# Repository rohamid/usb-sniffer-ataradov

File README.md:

# USB Sniffer #
This repository is for modified hardware of [ataradov's USB-sniffer](https://github.com/ataradov/usb-sniffer). I re-design this hardware because I don't want to use the 3d print case. I like to use the aluminum case.

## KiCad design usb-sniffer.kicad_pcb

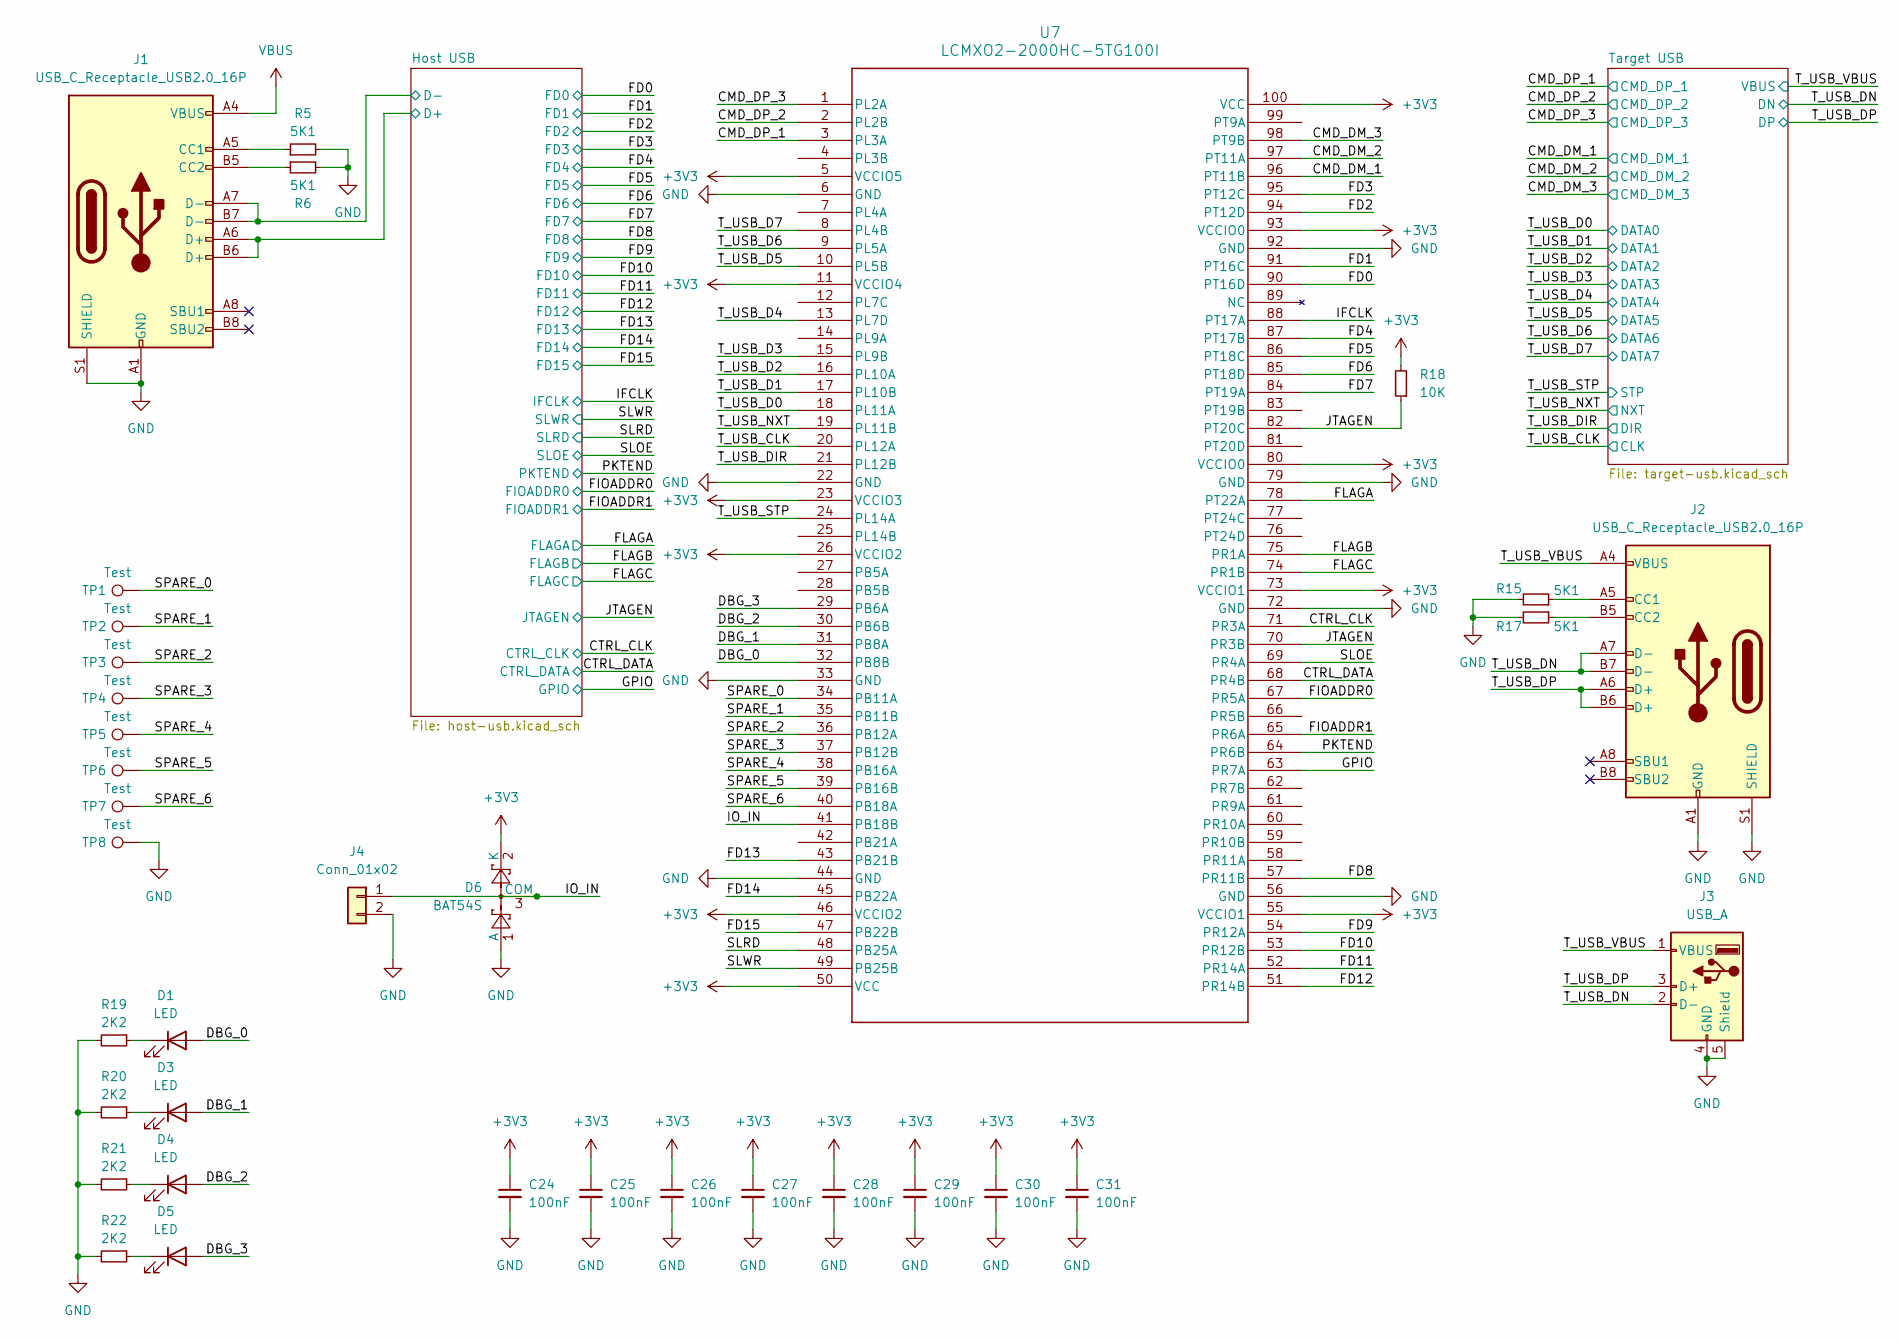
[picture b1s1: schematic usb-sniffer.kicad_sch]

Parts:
C24, C25, C26, C27, C28, C29, C30, C31: 100nF; C_0402_1005Metric
D1, D3, D4, D5: LED; LED_0603_1608Metric
D6: BAT54S; SOT-23
J1, J2: USB_C_Receptacle_USB2.0_16P; USB_C_Receptacle_G-Switch_GT-USB-7010ASV
J3: USB_A; USB_A_Molex_67643_Horizontal
J4: Conn_01x02; PinHeader_1x02_P2.54mm_Vertical
R5, R6, R15, R17: 5K1; R_0402_1005Metric
R18: 10K; R_0402_1005Metric
R19, R20, R21, R22: 2K2; R_0402_1005Metric
TP1, TP2, TP3, TP4, TP5, TP6, TP7, TP8: Test; TestPoint_Pad_D1.0mm
U7: LCMXO2-2000HC-5TG100I; LQFP-100_14x14mm_P0.5mm

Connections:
+3V3: C24.1, C25.1, C26.1, C27.1, C28.1, C29.1, C30.1, C31.1, D6.2 (K), R18.2, U7.5 (VCCIO5), U7.11 (VCCIO4), U7.23 (VCCIO3), U7.26 (VCCIO2), U7.46 (VCCIO2), U7.50 (VCC), U7.55 (VCCIO1), U7.73 (VCCIO1), U7.80 (VCCIO0), U7.93 (VCCIO0), U7.100 (VCC); also elsewhere on the board
/CMD_DM_1: U7.96 (PT11B); also elsewhere on the board
/CMD_DM_2: U7.97 (PT11A); also elsewhere on the board
/CMD_DM_3: U7.98 (PT9B); also elsewhere on the board
/CMD_DP_1: U7.3 (PL3A); also elsewhere on the board
/CMD_DP_2: U7.2 (PL2B); also elsewhere on the board
/CMD_DP_3: U7.1 (PL2A); also elsewhere on the board
/CTRL_CLK: U7.71 (PR3A); also elsewhere on the board
/CTRL_DATA: U7.68 (PR4B); also elsewhere on the board
/DBG_0: D1.2 (A), U7.32 (PB8B)
/DBG_1: D3.2 (A), U7.31 (PB8A)
/DBG_2: D4.2 (A), U7.30 (PB6B)
/DBG_3: D5.2 (A), U7.29 (PB6A)
/FD0: U7.90 (PT16D); also elsewhere on the board
/FD1: U7.91 (PT16C); also elsewhere on the board
/FD2: U7.94 (PT12D); also elsewhere on the board
/FD3: U7.95 (PT12C); also elsewhere on the board
/FD4: U7.87 (PT17B); also elsewhere on the board
/FD5: U7.86 (PT18C); also elsewhere on the board
/FD6: U7.85 (PT18D); also elsewhere on the board
/FD7: U7.84 (PT19A); also elsewhere on the board
/FD8: U7.57 (PR11B); also elsewhere on the board
/FD9: U7.54 (PR12A); also elsewhere on the board
/FD10: U7.53 (PR12B); also elsewhere on the board
/FD11: U7.52 (PR14A); also elsewhere on the board
/FD12: U7.51 (PR14B); also elsewhere on the board
/FD13: U7.43 (PB21B); also elsewhere on the board
/FD14: U7.45 (PB22A); also elsewhere on the board
/FD15: U7.47 (PB22B); also elsewhere on the board
/FIOADDR0: U7.67 (PR5A); also elsewhere on the board
/FIOADDR1: U7.65 (PR6A); also elsewhere on the board
/FLAGA: U7.78 (PT22A); also elsewhere on the board
/FLAGB: U7.75 (PR1A); also elsewhere on the board
/FLAGC: U7.74 (PR1B); also elsewhere on the board
/GPIO: U7.63 (PR7A); also elsewhere on the board
/Host USB/D+: J1.A6 (D+), J1.B6 (D+); also elsewhere on the board
/Host USB/D-: J1.A7 (D-), J1.B7 (D-); also elsewhere on the board
/IFCLK: U7.88 (PT17A); also elsewhere on the board
/IO_IN: D6.3 (COM), J4.1, U7.41 (PB18B)
/JTAGEN: R18.1, U7.70 (PR3B), U7.82 (PT20C); also elsewhere on the board
/PKTEND: U7.64 (PR6B); also elsewhere on the board
/SLOE: U7.69 (PR4A); also elsewhere on the board
/SLRD: U7.48 (PB25A); also elsewhere on the board
/SLWR: U7.49 (PB25B); also elsewhere on the board
/SPARE_0: TP1.1, U7.34 (PB11A)
/SPARE_1: TP2.1, U7.35 (PB11B)
/SPARE_2: TP3.1, U7.36 (PB12A)
/SPARE_3: TP4.1, U7.37 (PB12B)
/SPARE_4: TP5.1, U7.38 (PB16A)
/SPARE_5: TP6.1, U7.39 (PB16B)
/SPARE_6: TP7.1, U7.40 (PB18A)
/T_USB_CLK: U7.20 (PL12A); also elsewhere on the board
/T_USB_D0: U7.18 (PL11A); also elsewhere on the board
/T_USB_D1: U7.17 (PL10B); also elsewhere on the board
/T_USB_D2: U7.16 (PL10A); also elsewhere on the board
/T_USB_D3: U7.15 (PL9B); also elsewhere on the board
/T_USB_D4: U7.13 (PL7D); also elsewhere on the board
/T_USB_D5: U7.10 (PL5B); also elsewhere on the board
/T_USB_D6: U7.9 (PL5A); also elsewhere on the board
/T_USB_D7: U7.8 (PL4B); also elsewhere on the board
/T_USB_DIR: U7.21 (PL12B); also elsewhere on the board
/T_USB_DN: J2.A7 (D-), J2.B7 (D-), J3.2 (D-); also elsewhere on the board
/T_USB_DP: J2.A6 (D+), J2.B6 (D+), J3.3 (D+); also elsewhere on the board
/T_USB_NXT: U7.19 (PL11B); also elsewhere on the board
/T_USB_STP: U7.24 (PL14A); also elsewhere on the board
/T_USB_VBUS: J2.A4 (VBUS), J2.A9 (VBUS), J2.B4 (VBUS), J2.B9 (VBUS), J3.1 (VBUS); also elsewhere on the board
GND: C24.2, C25.2, C26.2, C27.2, C28.2, C29.2, C30.2, C31.2, D6.1 (A), J1.A1 (GND), J1.A12 (GND), J1.B1 (GND), J1.B12 (GND), J1.S1 (SHIELD), J2.A1 (GND), J2.A12 (GND), J2.B1 (GND), J2.B12 (GND), J2.S1 (SHIELD), J3.4 (GND), J3.5 (Shield), J4.2, R5.2, R6.2, R15.2, R17.2, R19.2, R20.2, R21.2, R22.2, TP8.1, U7.6 (GND), U7.22 (GND), U7.33 (GND), U7.44 (GND), U7.56 (GND), U7.72 (GND), U7.79 (GND), U7.92 (GND); also elsewhere on the board
unnamed: D1.1 (K), R19.1
unnamed: D3.1 (K), R20.1
unnamed: D4.1 (K), R21.1
unnamed: D5.1 (K), R22.1
unnamed: J1.A5 (CC1), R5.1
unnamed: J1.B5 (CC2), R6.1
unnamed: J2.A5 (CC1), R15.1
unnamed: J2.B5 (CC2), R17.1
VBUS: J1.A4 (VBUS), J1.A9 (VBUS), J1.B4 (VBUS), J1.B9 (VBUS)

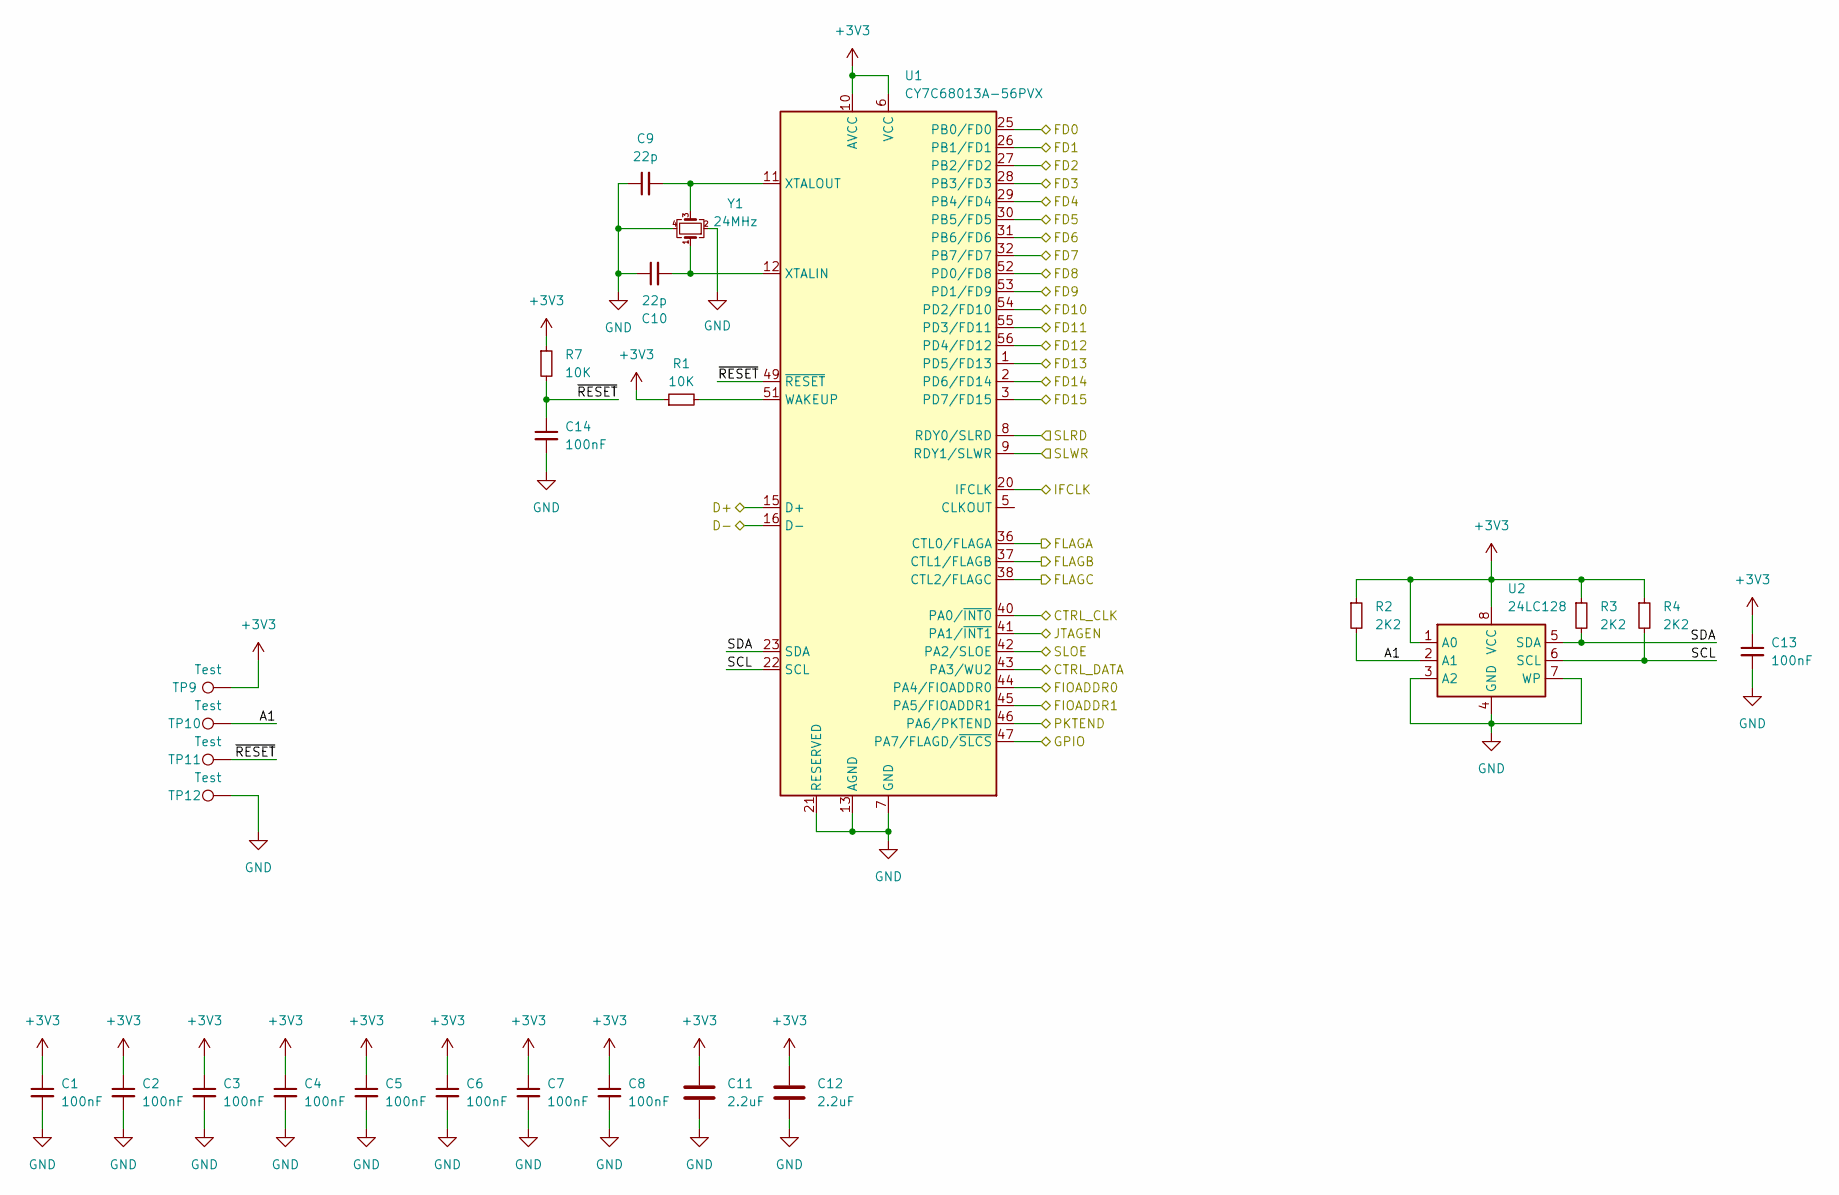
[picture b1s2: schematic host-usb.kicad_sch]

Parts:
C1, C2, C3, C4, C5, C6, C7, C8, C13, C14: 100nF; C_0402_1005Metric
C9, C10: 22p; C_0402_1005Metric
C11, C12: 2.2uF; C_0603_1608Metric
R1, R7: 10K; R_0402_1005Metric
R2, R3, R4: 2K2; R_0402_1005Metric
TP9, TP10, TP11, TP12: Test; TestPoint_Pad_D1.0mm
U1: CY7C68013A-56PVX; SSOP-56_7.5x18.5mm_P0.635mm
U2: 24LC128; SOIC-8_3.9x4.9mm_P1.27mm
Y1: 24MHz; Crystal_SMD_3225-4Pin_3.2x2.5mm

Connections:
+3V3: C1.1, C2.1, C3.1, C4.1, C5.1, C6.1, C7.1, C8.1, C11.1, C12.1, C13.1, R1.1, R2.1, R3.1, R4.1, R7.1, TP9.1, U1.6 (VCC), U1.10 (AVCC), U1.14 (AVCC), U1.18 (VCC), U1.24 (VCC), U1.34 (VCC), U1.39 (VCC), U1.50 (VCC), U2.1 (A0), U2.8 (VCC); also elsewhere on the board
/CTRL_CLK: U1.40 (PA0/~INT0); also elsewhere on the board
/CTRL_DATA: U1.43 (PA3/WU2); also elsewhere on the board
/FD0: U1.25 (PB0/FD0); also elsewhere on the board
/FD1: U1.26 (PB1/FD1); also elsewhere on the board
/FD2: U1.27 (PB2/FD2); also elsewhere on the board
/FD3: U1.28 (PB3/FD3); also elsewhere on the board
/FD4: U1.29 (PB4/FD4); also elsewhere on the board
/FD5: U1.30 (PB5/FD5); also elsewhere on the board
/FD6: U1.31 (PB6/FD6); also elsewhere on the board
/FD7: U1.32 (PB7/FD7); also elsewhere on the board
/FD8: U1.52 (PD0/FD8); also elsewhere on the board
/FD9: U1.53 (PD1/FD9); also elsewhere on the board
/FD10: U1.54 (PD2/FD10); also elsewhere on the board
/FD11: U1.55 (PD3/FD11); also elsewhere on the board
/FD12: U1.56 (PD4/FD12); also elsewhere on the board
/FD13: U1.1 (PD5/FD13); also elsewhere on the board
/FD14: U1.2 (PD6/FD14); also elsewhere on the board
/FD15: U1.3 (PD7/FD15); also elsewhere on the board
/FIOADDR0: U1.44 (PA4/FIOADDR0); also elsewhere on the board
/FIOADDR1: U1.45 (PA5/FIOADDR1); also elsewhere on the board
/FLAGA: U1.36 (CTL0/FLAGA); also elsewhere on the board
/FLAGB: U1.37 (CTL1/FLAGB); also elsewhere on the board
/FLAGC: U1.38 (CTL2/FLAGC); also elsewhere on the board
/GPIO: U1.47 (PA7/FLAGD/~SLCS); also elsewhere on the board
/Host USB/A1: R2.2, TP10.1, U2.2 (A1)
/Host USB/D+: U1.15 (D+); also elsewhere on the board
/Host USB/D-: U1.16 (D-); also elsewhere on the board
/Host USB/SCL: R4.2, U1.22 (SCL), U2.6 (SCL)
/Host USB/SDA: R3.2, U1.23 (SDA), U2.5 (SDA)
/Host USB/~RESET: C14.1, R7.2, TP11.1, U1.49 (~RESET)
/IFCLK: U1.20 (IFCLK); also elsewhere on the board
/JTAGEN: U1.41 (PA1/~INT1); also elsewhere on the board
/PKTEND: U1.46 (PA6/PKTEND); also elsewhere on the board
/SLOE: U1.42 (PA2/SLOE); also elsewhere on the board
/SLRD: U1.8 (RDY0/SLRD); also elsewhere on the board
/SLWR: U1.9 (RDY1/SLWR); also elsewhere on the board
GND: C1.2, C2.2, C3.2, C4.2, C5.2, C6.2, C7.2, C8.2, C9.1, C10.1, C11.2, C12.2, C13.2, C14.2, TP12.1, U1.4 (GND), U1.7 (GND), U1.13 (AGND), U1.17 (AGND), U1.19 (GND), U1.21 (RESERVED), U1.33 (GND), U1.35 (GND), U1.48 (GND), U2.3 (A2), U2.4 (GND), U2.7 (WP), Y1.2, Y1.4; also elsewhere on the board
unnamed: R1.2, U1.51 (WAKEUP)
unnamed: C10.2, U1.12 (XTALIN), Y1.1
unnamed: C9.2, U1.11 (XTALOUT), Y1.3

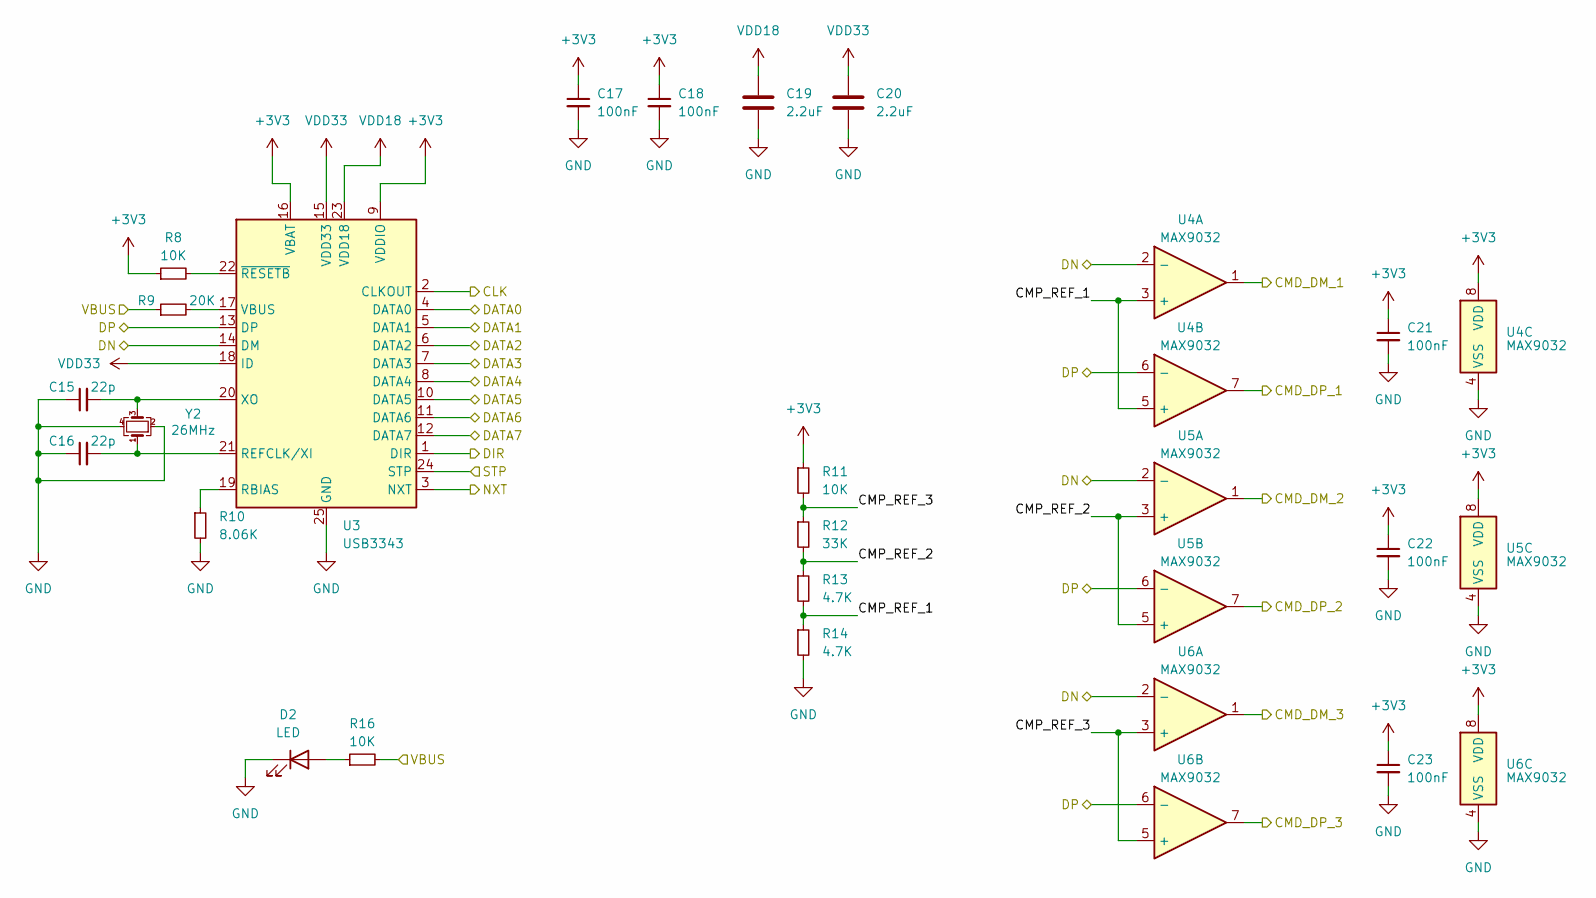
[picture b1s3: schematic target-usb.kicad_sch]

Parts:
C15, C16: 22p; C_0402_1005Metric
C17, C18, C21, C22, C23: 100nF; C_0402_1005Metric
C19, C20: 2.2uF; C_0603_1608Metric
D2: LED; LED_0603_1608Metric
R8, R11, R16: 10K; R_0402_1005Metric
R9: 20K; R_0402_1005Metric
R10: 8.06K; R_0402_1005Metric
R12: 33K; R_0402_1005Metric
R13, R14: 4.7K; R_0402_1005Metric
U3: USB3343; QFN-24-1EP_4x4mm_P0.5mm_EP2.6x2.6mm
U4, U5, U6: MAX9032; SOT-23-8
Y2: 26MHz; Crystal_SMD_3225-4Pin_3.2x2.5mm

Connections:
+3V3: C17.1, C18.1, C21.1, C22.1, C23.1, R8.1, R11.1, U3.9 (VDDIO), U3.16 (VBAT), U4.8 (VDD), U5.8 (VDD), U6.8 (VDD); also elsewhere on the board
/CMD_DM_1: U4.1; also elsewhere on the board
/CMD_DM_2: U5.1; also elsewhere on the board
/CMD_DM_3: U6.1; also elsewhere on the board
/CMD_DP_1: U4.7; also elsewhere on the board
/CMD_DP_2: U5.7; also elsewhere on the board
/CMD_DP_3: U6.7; also elsewhere on the board
/T_USB_CLK: U3.2 (CLKOUT); also elsewhere on the board
/T_USB_D0: U3.4 (DATA0); also elsewhere on the board
/T_USB_D1: U3.5 (DATA1); also elsewhere on the board
/T_USB_D2: U3.6 (DATA2); also elsewhere on the board
/T_USB_D3: U3.7 (DATA3); also elsewhere on the board
/T_USB_D4: U3.8 (DATA4); also elsewhere on the board
/T_USB_D5: U3.10 (DATA5); also elsewhere on the board
/T_USB_D6: U3.11 (DATA6); also elsewhere on the board
/T_USB_D7: U3.12 (DATA7); also elsewhere on the board
/T_USB_DIR: U3.1 (DIR); also elsewhere on the board
/T_USB_DN: U3.14 (DM), U4.2 (-), U5.2 (-), U6.2 (-); also elsewhere on the board
/T_USB_DP: U3.13 (DP), U4.6 (-), U5.6 (-), U6.6 (-); also elsewhere on the board
/T_USB_NXT: U3.3 (NXT); also elsewhere on the board
/T_USB_STP: U3.24 (STP); also elsewhere on the board
/T_USB_VBUS: R9.1, R16.2; also elsewhere on the board
/Target USB/CMP_REF_1: R13.2, R14.1, U4.3 (+), U4.5 (+)
/Target USB/CMP_REF_2: R12.2, R13.1, U5.3 (+), U5.5 (+)
/Target USB/CMP_REF_3: R11.2, R12.1, U6.3 (+), U6.5 (+)
GND: C15.1, C16.1, C17.2, C18.2, C19.2, C20.2, C21.2, C22.2, C23.2, D2.1 (K), R10.2, R14.2, U3.25 (GND), U4.4 (VSS), U5.4 (VSS), U6.4 (VSS), Y2.2, Y2.4; also elsewhere on the board
unnamed: D2.2 (A), R16.1
unnamed: R10.1, U3.19 (RBIAS)
unnamed: C16.2, U3.21 (REFCLK/XI), Y2.1
unnamed: R9.2, U3.17 (VBUS)
unnamed: C15.2, U3.20 (XO), Y2.3
unnamed: R8.2, U3.22 (~RESETB)
VDD18: C19.1, U3.23 (VDD18)
VDD33: C20.1, U3.15 (VDD33), U3.18 (ID)

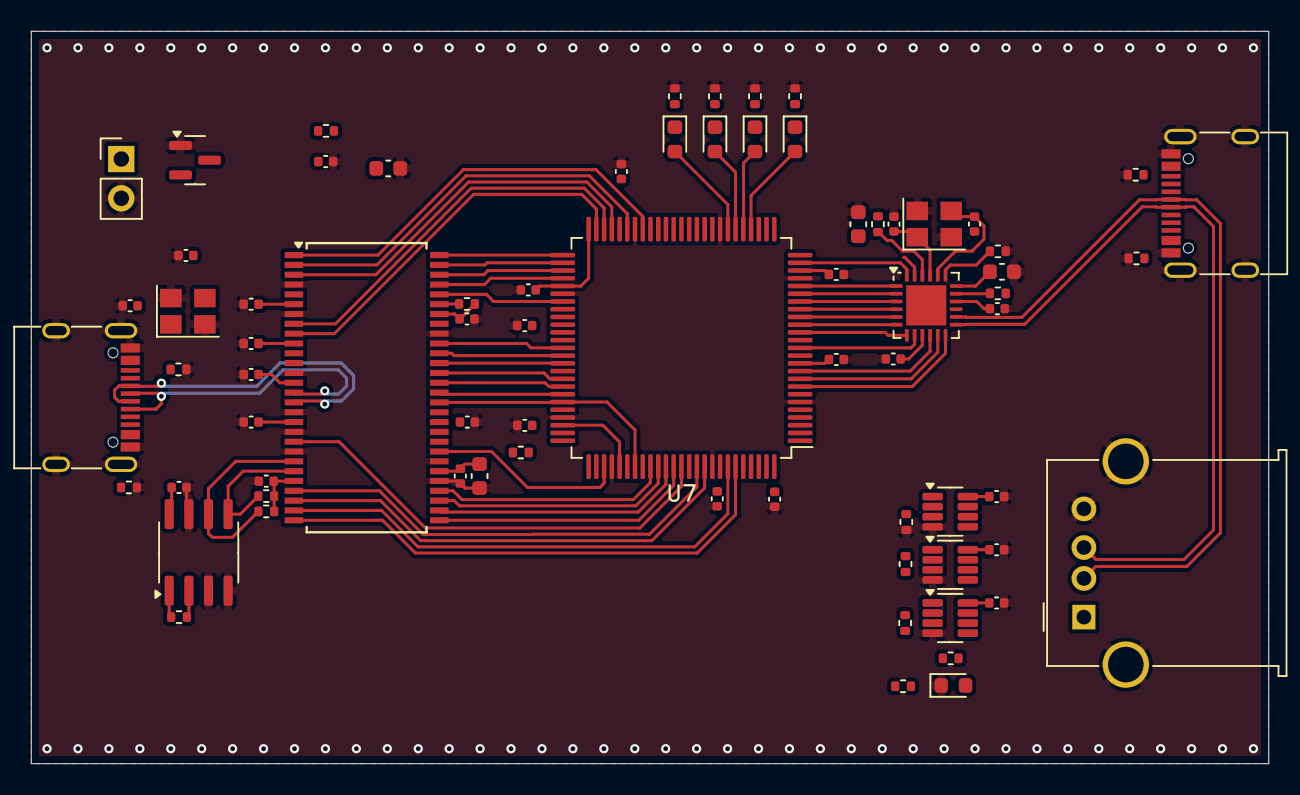
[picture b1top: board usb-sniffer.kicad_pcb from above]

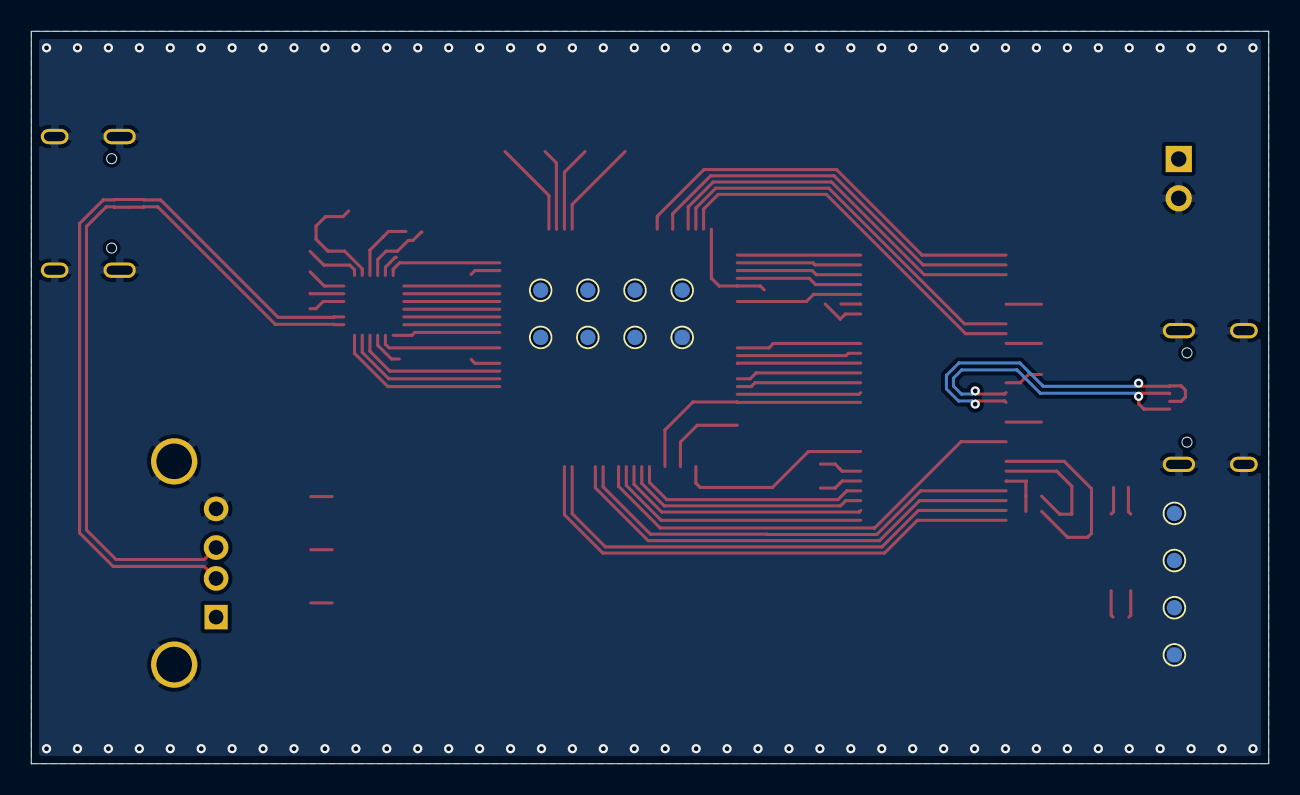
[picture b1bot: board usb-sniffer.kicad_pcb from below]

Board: 4 copper layers, 80.0 x 47.4 mm, 84 parts (12 on the bottom side), 94 nets.

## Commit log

2024-02-28 modified .gitignore
2024-03-04 Add USB3343
2024-04-01 layout uncompleted
2024-04-02 add side ground
